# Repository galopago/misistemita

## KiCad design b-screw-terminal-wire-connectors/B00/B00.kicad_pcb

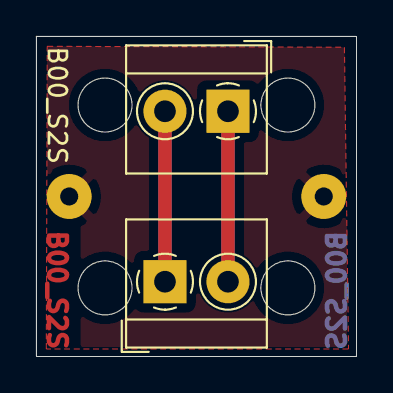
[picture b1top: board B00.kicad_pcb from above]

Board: 2 copper layers, 17.8 x 17.8 mm, 8 parts (0 on the bottom side), 3 nets.

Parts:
HA0, HA1: MountingHole; MountingHole_3mm
HB0, HB1: MountingHole; MountingHole_3mm
J0, J1: Conn_01x01_Male; SolderWirePad_1x01_Drill1mm
J2, J3: Conn_01x02_Female; TerminalBlock_4Ucon_1x02_P3.50mm_Horizontal

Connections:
unnamed: J0.1, J1.1
unnamed: J2.1, J3.2
unnamed: J2.2, J3.1

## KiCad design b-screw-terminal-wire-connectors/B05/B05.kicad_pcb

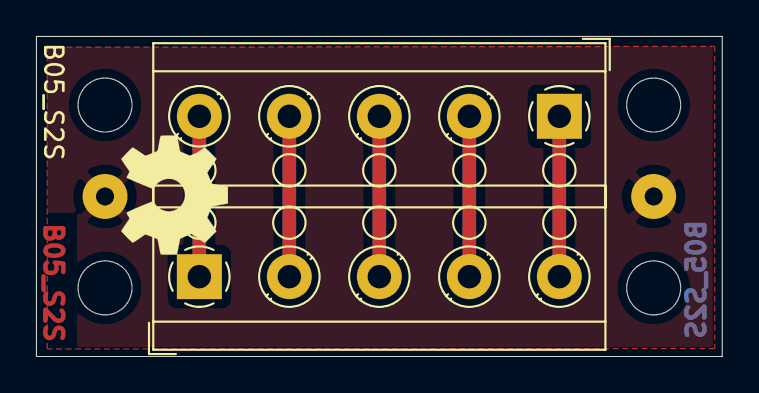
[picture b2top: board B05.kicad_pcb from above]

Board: 2 copper layers, 38.1 x 17.8 mm, 8 parts (0 on the bottom side), 6 nets.

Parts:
HA0, HA3: MountingHole; MountingHole_3mm
HB0, HB3: MountingHole; MountingHole_3mm
J0, J1: Conn_01x01_Male; SolderWirePad_1x01_Drill1mm
J2, J3: Conn_01x05_Female; TerminalBlock_RND_205-00004_1x05_P5.00mm_Horizontal

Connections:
unnamed: J0.1, J1.1
unnamed: J2.1, J3.5
unnamed: J2.2, J3.4
unnamed: J2.3, J3.3
unnamed: J2.4, J3.2
unnamed: J2.5, J3.1

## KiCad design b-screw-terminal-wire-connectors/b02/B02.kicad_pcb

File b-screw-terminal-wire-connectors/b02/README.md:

# 2x7 3.5 mm SCREW TERMINAL BOARD

For cable marshalling, make connections to external power/sensors in an organized way

Board with screw terminals soldered                                        |Bare single PCB|Panelized PCB|
---------------------------------------------------------------------------|---------------|-------------|
||

## Usage example 1

Power input and external powered sensor, i.e. I2C, SPI, RS485, etc. Up to 3 signal wires, plus power and ground for the sensor. Quick and easy commissioning thanks to the power connections for the sensor already carried out the right side of the screw terminal.

Single connection point|Single point close-up|Power wires connected|Board fixed to enclosure|
-----------------------|---------------------|---------------------|------------------------|
||||

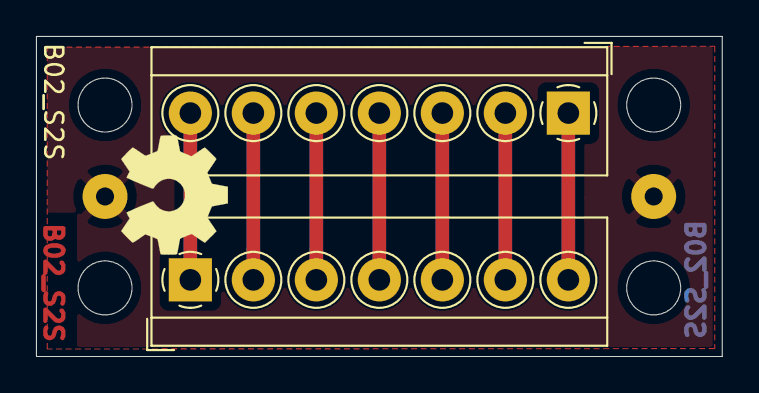
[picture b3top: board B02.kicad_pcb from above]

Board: 2 copper layers, 38.1 x 17.8 mm, 8 parts (0 on the bottom side), 8 nets.

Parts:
HA0, HA3: MountingHole; MountingHole_3mm
HB0, HB3: MountingHole; MountingHole_3mm
J0, J1: Conn_01x01_Male; SolderWirePad_1x01_Drill1mm
J4, J5: Conn_01x07_Female; TerminalBlock_4Ucon_1x07_P3.50mm_Horizontal

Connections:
unnamed: J0.1, J1.1
unnamed: J4.1, J5.7
unnamed: J4.2, J5.6
unnamed: J4.3, J5.5
unnamed: J4.4, J5.4
unnamed: J4.5, J5.3
unnamed: J4.6, J5.2
unnamed: J4.7, J5.1

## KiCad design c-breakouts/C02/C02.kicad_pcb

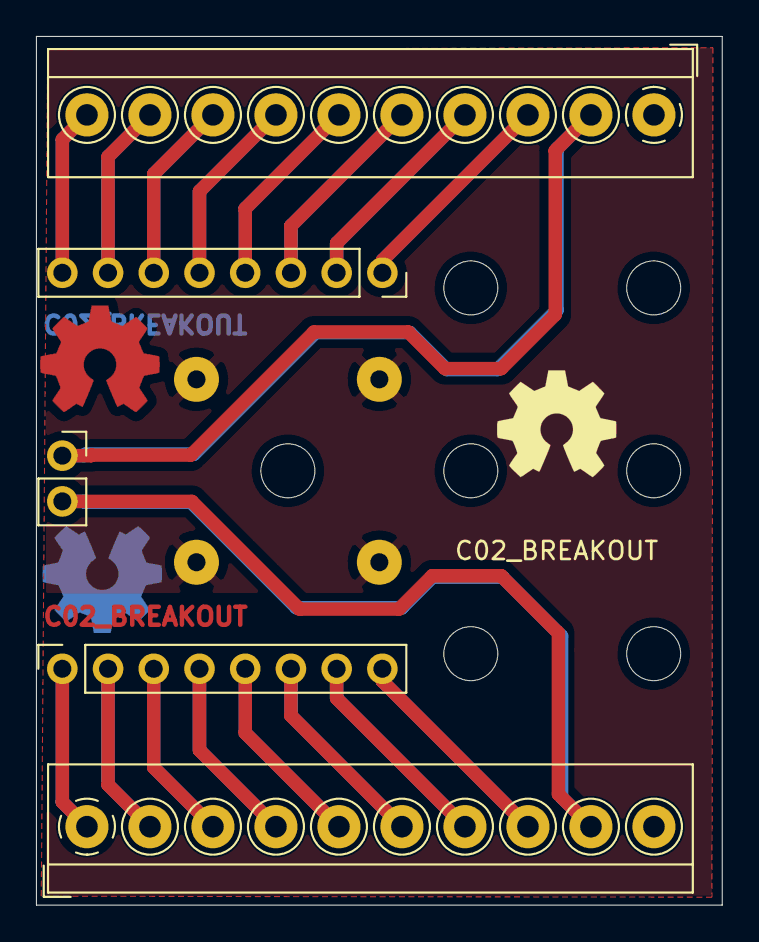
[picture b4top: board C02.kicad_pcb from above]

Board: 2 copper layers, 38.1 x 48.3 mm, 16 parts (0 on the bottom side), 19 nets.

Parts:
HB2, HB3: MountingHole; MountingHole_3mm
HC1, HC2, HC3: MountingHole; MountingHole_3mm
HD2, HD3: MountingHole; MountingHole_3mm
J0, J1, J2, J3: Conn_01x01_Male; SolderWirePad_1x01_Drill1mm
J4, J5: Conn_01x10_Female; TerminalBlock_4Ucon_1x10_P3.50mm_Horizontal
J6, J8: Conn_01x08_Female; PinSocket_1x08_P2.54mm_Vertical
J7: Conn_01x02_Female; PinSocket_1x02_P2.54mm_Vertical

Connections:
unnamed: J0.1, J1.1, J2.1, J3.1
unnamed: J4.2, J7.1
unnamed: J4.3, J8.1
unnamed: J4.4, J8.2
unnamed: J4.5, J8.3
unnamed: J4.6, J8.4
unnamed: J4.7, J8.5
unnamed: J4.8, J8.6
unnamed: J4.9, J8.7
unnamed: J4.10, J8.8
unnamed: J5.1, J6.1
unnamed: J5.2, J6.2
unnamed: J5.3, J6.3
unnamed: J5.4, J6.4
unnamed: J5.5, J6.5
unnamed: J5.6, J6.6
unnamed: J5.7, J6.7
unnamed: J5.8, J6.8
unnamed: J5.9, J7.2

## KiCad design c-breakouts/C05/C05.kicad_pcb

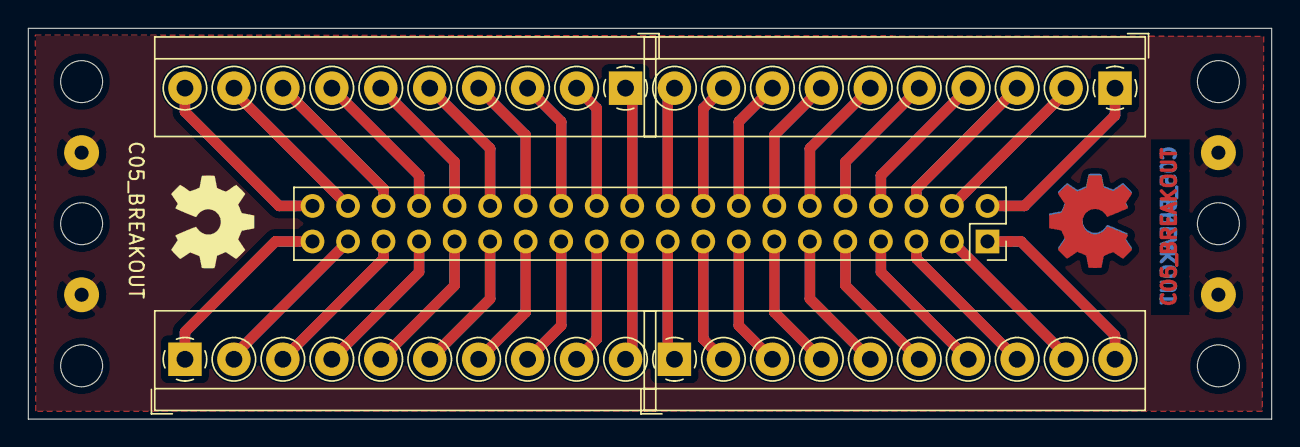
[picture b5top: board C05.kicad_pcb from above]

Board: 2 copper layers, 88.9 x 27.9 mm, 15 parts (0 on the bottom side), 41 nets.

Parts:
HA0, HA8: MountingHole; MountingHole_3mm
HB0, HB8: MountingHole; MountingHole_3mm
HC0, HC8: MountingHole; MountingHole_3mm
J0, J1, J2, J3: Conn_01x01_Male; SolderWirePad_1x01_Drill1mm
J4, J6, J7, J8: Conn_01x10_Female; TerminalBlock_4Ucon_1x10_P3.50mm_Horizontal
J5: Conn_02x20_Odd_Even; PinSocket_2x20_P2.54mm_Vertical

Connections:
unnamed: J0.1, J1.1, J2.1, J3.1
unnamed: J4.1, J5.19
unnamed: J4.2, J5.17
unnamed: J4.3, J5.15
unnamed: J4.4, J5.13
unnamed: J4.5, J5.11
unnamed: J4.6, J5.9
unnamed: J4.7, J5.7
unnamed: J4.8, J5.5
unnamed: J4.9, J5.3
unnamed: J4.10, J5.1
unnamed: J5.2, J7.1
unnamed: J5.4, J7.2
unnamed: J5.6, J7.3
unnamed: J5.8, J7.4
unnamed: J5.10, J7.5
unnamed: J5.12, J7.6
unnamed: J5.14, J7.7
unnamed: J5.16, J7.8
unnamed: J5.18, J7.9
unnamed: J5.20, J7.10
unnamed: J5.21, J6.10
unnamed: J5.22, J8.1
unnamed: J5.23, J6.9
unnamed: J5.24, J8.2
unnamed: J5.25, J6.8
unnamed: J5.26, J8.3
unnamed: J5.27, J6.7
unnamed: J5.28, J8.4
unnamed: J5.29, J6.6
unnamed: J5.30, J8.5
unnamed: J5.31, J6.5
unnamed: J5.32, J8.6
unnamed: J5.33, J6.4
unnamed: J5.34, J8.7
unnamed: J5.35, J6.3
unnamed: J5.36, J8.8
unnamed: J5.37, J6.2
unnamed: J5.38, J8.9
unnamed: J5.39, J6.1
unnamed: J5.40, J8.10

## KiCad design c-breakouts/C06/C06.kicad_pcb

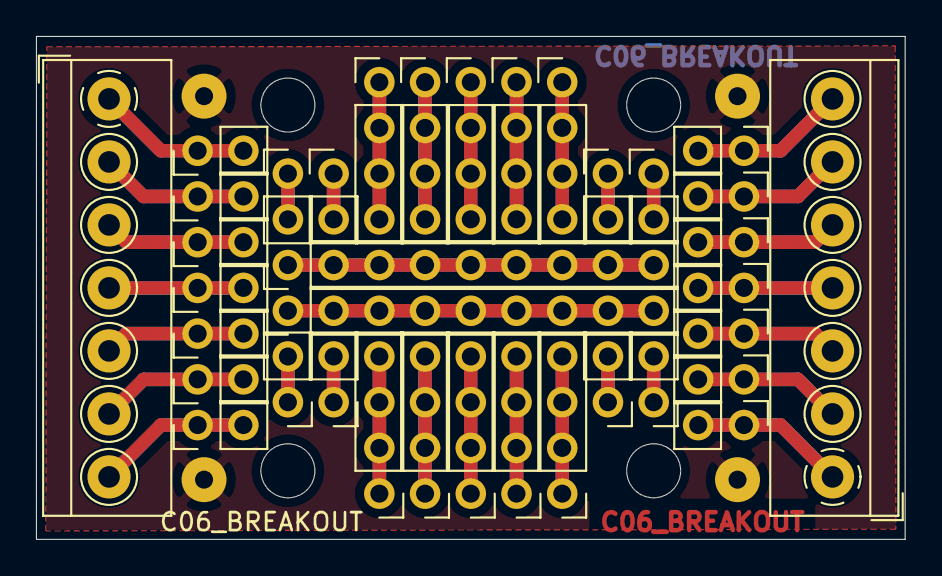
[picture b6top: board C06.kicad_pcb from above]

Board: 2 copper layers, 48.3 x 27.9 mm, 44 parts (0 on the bottom side), 35 nets.

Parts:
HA1, HA3: MountingHole; MountingHole_3mm
HC1, HC3: MountingHole; MountingHole_3mm
J1, J2, J3, J6, J9, J10, J11, J12, J13, J14, J15, J16, J17, J18, J19, J20, J21, J22, J23, J24, J25, J26: Conn_01x02_Female; PinHeader_1x02_P2.54mm_Vertical
J4, J5: Conn_01x07_Female; TerminalBlock_4Ucon_1x07_P3.50mm_Horizontal
J7, J8: Conn_01x09_Female; PinHeader_1x09_P2.54mm_Vertical
J27, J28, J29, J30, J31, J32, J33, J34, J35, J36: Conn_01x04_Female; PinHeader_1x04_P2.54mm_Vertical
J37, J38, J39, J40: Conn_01x01_Male; SolderWirePad_1x01_Drill1mm

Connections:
unnamed: J1.1, J1.2, J4.1
unnamed: J2.1, J2.2, J4.2
unnamed: J3.1, J3.2, J5.7
unnamed: J5.6, J6.1, J6.2
unnamed: J7.1, J7.2, J7.3, J7.4, J7.5, J7.6, J7.7, J7.8, J7.9
unnamed: J8.1, J8.2, J8.3, J8.4, J8.5, J8.6, J8.7, J8.8, J8.9
unnamed: J9.1, J9.2
unnamed: J10.1, J10.2
unnamed: J4.3, J11.1, J11.2
unnamed: J4.4, J12.1, J12.2
unnamed: J4.5, J13.1, J13.2
unnamed: J4.6, J14.1, J14.2
unnamed: J4.7, J15.1, J15.2
unnamed: J5.5, J16.1, J16.2
unnamed: J5.4, J17.1, J17.2
unnamed: J5.3, J18.1, J18.2
unnamed: J5.2, J19.1, J19.2
unnamed: J5.1, J20.1, J20.2
unnamed: J21.1, J21.2
unnamed: J22.1, J22.2
unnamed: J23.1, J23.2
unnamed: J24.1, J24.2
unnamed: J25.1, J25.2
unnamed: J26.1, J26.2
unnamed: J27.1, J27.2, J27.3, J27.4
unnamed: J28.1, J28.2, J28.3, J28.4
unnamed: J29.1, J29.2, J29.3, J29.4
unnamed: J30.1, J30.2, J30.3, J30.4
unnamed: J31.1, J31.2, J31.3, J31.4
unnamed: J32.1, J32.2, J32.3, J32.4
unnamed: J33.1, J33.2, J33.3, J33.4
unnamed: J34.1, J34.2, J34.3, J34.4
unnamed: J35.1, J35.2, J35.3, J35.4
unnamed: J36.1, J36.2, J36.3, J36.4
unnamed: J37.1, J38.1, J39.1, J40.1
